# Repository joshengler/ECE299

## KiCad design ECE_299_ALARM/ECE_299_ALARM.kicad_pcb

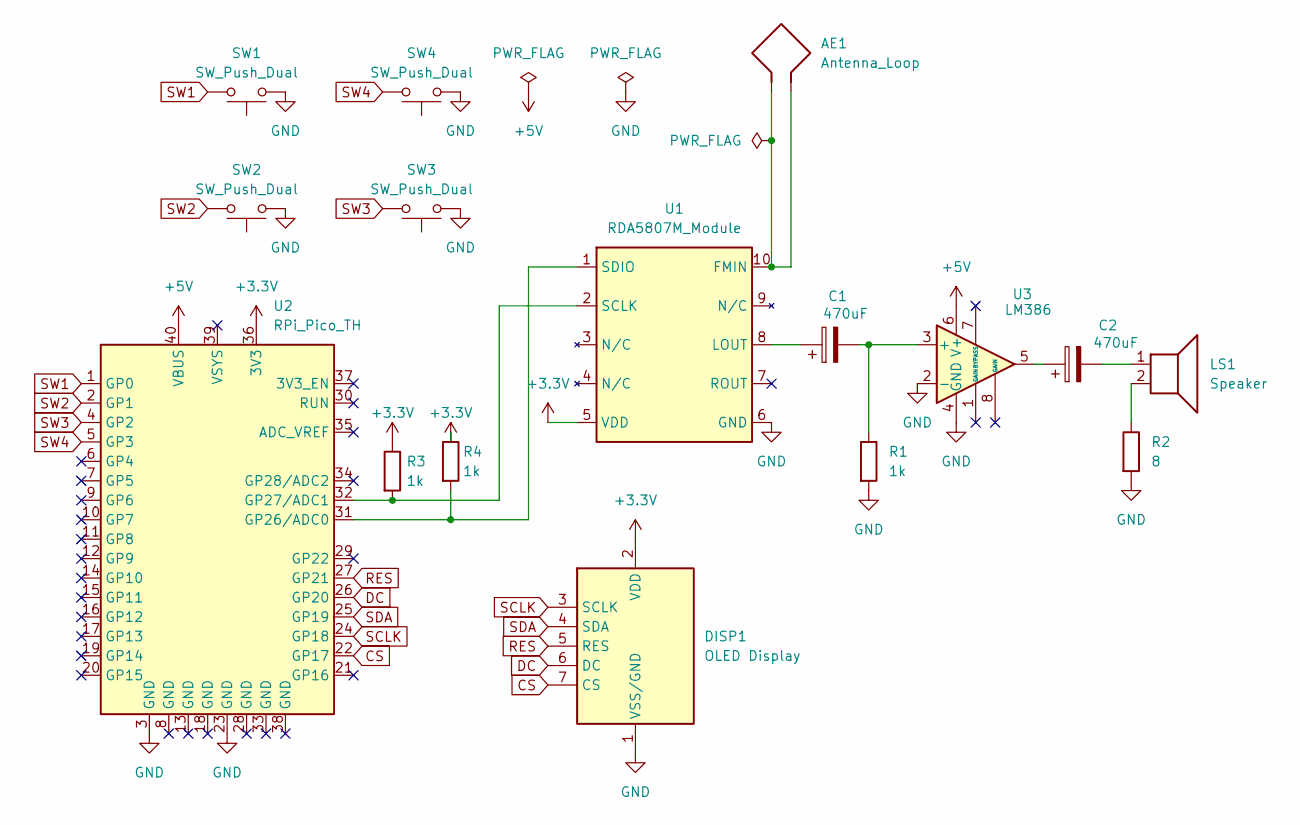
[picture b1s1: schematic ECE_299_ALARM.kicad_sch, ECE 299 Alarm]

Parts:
AE1: Antenna_Loop; PinHeader_1x02_P1.00mm_Vertical
C1, C2: 470uF; C_Radial_D6.3mm_H11.0mm_P2.50mm
DISP1: OLED Display; OLED_Display_1.3
LS1: Speaker; PinHeader_1x02_P2.54mm_Vertical
R1, R3, R4: 1k; R_Axial_DIN0309_L9.0mm_D3.2mm_P12.70mm_Horizontal
R2: 8; R_Axial_DIN0309_L9.0mm_D3.2mm_P12.70mm_Horizontal
SW1, SW2, SW3, SW4: SW_Push_Dual; SW_PUSH_6mm_H4.3mm
U1: RDA5807M_Module; RDA5807M_Module_SM
U2: RPi_Pico_TH
U3: LM386; DIP-8_W7.62mm

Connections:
+3.3V: DISP1.2 (VDD), R3.1, R4.1, U1.5 (VDD), U2.36 (3V3)
+5V: U2.40 (VBUS), U3.6 (V+)
CS: DISP1.7 (CS), U2.22 (GP17)
DC: DISP1.6 (DC), U2.26 (GP20)
GND: DISP1.1 (VSS/GND), R1.2, R2.2, SW1.1, SW2.1, SW3.1, SW4.1, U1.6 (GND), U2.3 (GND), U2.23 (GND), U3.2 (-), U3.4 (GND)
unnamed: C2.1, U3.5
unnamed: C2.2, LS1.1
unnamed: LS1.2, R2.1
unnamed: AE1.1, AE1.2, U1.10 (FMIN)
unnamed: C1.1, U1.8 (LOUT)
unnamed: R3.2, U1.2 (SCLK), U2.32 (GP27/ADC1)
unnamed: R4.2, U1.1 (SDIO), U2.31 (GP26/ADC0)
unnamed: C1.2, R1.1, U3.3 (+)
RES: DISP1.5 (RES), U2.27 (GP21)
SCLK: DISP1.3 (SCLK), U2.24 (GP18)
SDA: DISP1.4 (SDA), U2.25 (GP19)
SW1: SW1.2, U2.1 (GP0)
SW2: SW2.2, U2.2 (GP1)
SW3: SW3.2, U2.4 (GP2)
SW4: SW4.2, U2.5 (GP3)

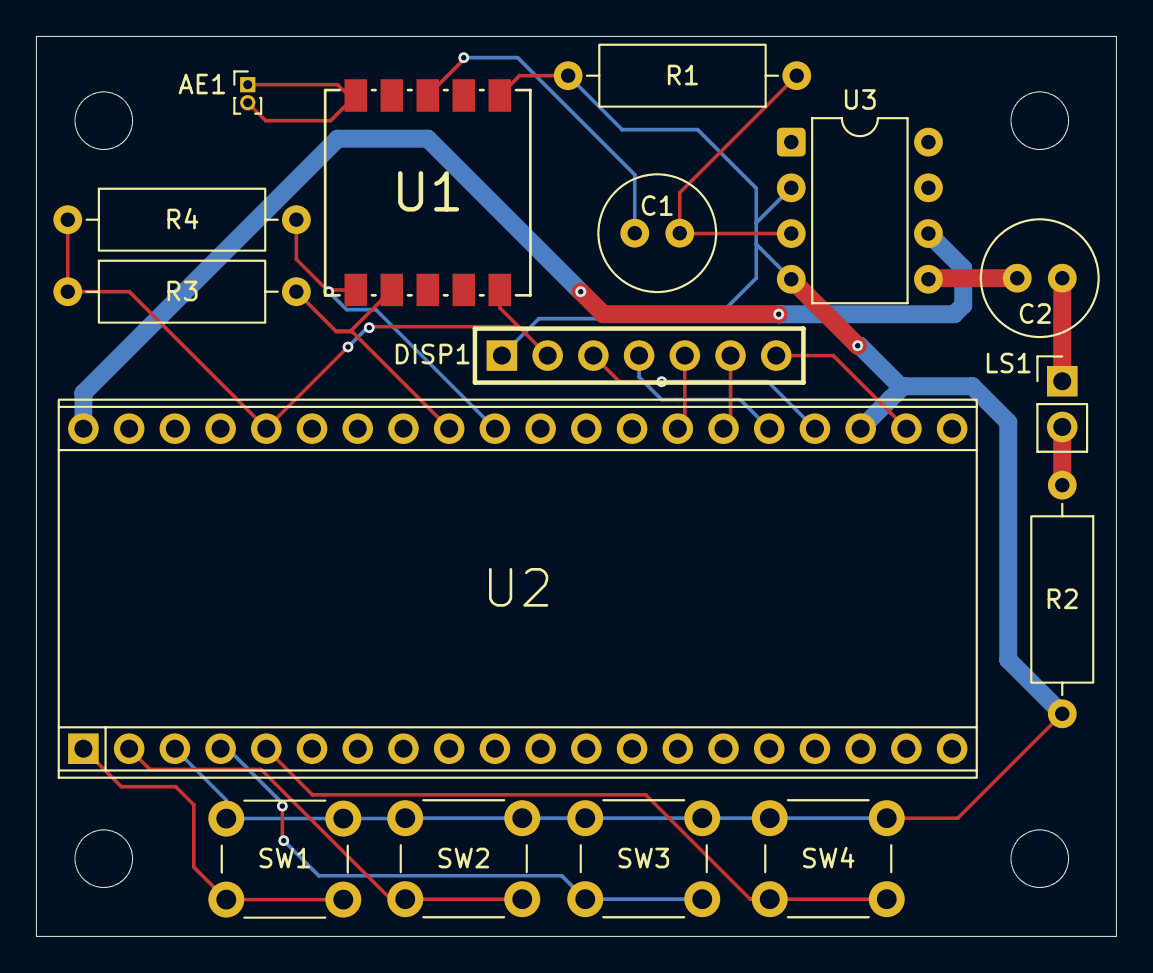
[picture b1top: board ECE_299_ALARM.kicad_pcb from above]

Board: 2 copper layers, 60.0 x 50.0 mm, 16 parts (0 on the bottom side), 20 nets.

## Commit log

2025-06-17 add vol, freq and mute controls to radio, still buggy but poc
2025-06-18 add vscode build, to avoid using thonny. requires mpremote
2025-06-18 fix vscode console output
2025-06-18 switch to alternative library, somehow the waveforms are cleaner on this lib, this library also gives better low level control + RDS
2025-06-18 various audio quality fixes, some cleanup
2025-06-18 add RSSI
2025-06-18 scuffed RDS implementation, very buggy atm
2025-06-18 remove rds, clean up dead/old code
2025-06-18 working rds support, needs strong signal tho
2025-06-18 disable rds for now
2025-06-20 add start of schematic
2025-06-22 added web app files
2025-06-22 commented out radio dependencies because my board doesnt have a radio module
2025-06-22 fixed URL from resubmitting queries when reloading the webpage
2025-06-22 moved html, css, js files a singular folder
2025-06-24 finish schematic
2025-06-24 remove lock
2025-06-24 add pullups on i2c
2025-06-24 fix antenna footprint
2025-06-24 fix antenna footprint (fr this time) also fix button footprint to be 2
2025-06-24 fix lm386-4 footprint
2025-06-24 garbage routing job completed
2025-06-25 add title and other info to sheet
2025-06-28 fixed typos
2025-06-28 browser should poll the board for any settings modified through hardware and update as needed
2025-07-07 added styles
2025-07-07 added support for changing alarm settings through a web interface
2025-07-09 added pcb files
2025-07-09 Revert "Web app"
2025-07-14 fix silkscreen overlap
2025-07-14 generate gerbers + drill
2025-07-25 error handling for radio and update pcb
2025-07-26 fix swapped SDA and SCL on radio module
2025-07-26 i just wasted an hour making better routing
2025-07-26 add high current path, 1mm is probably excessive
2025-07-26 small_adjustments
2025-07-26 realized i also need to make the power supply lines wider too...
2025-07-26 regenerate gerbers and drills
2025-07-26 remove locks
2025-07-26 add bar graph, STOP SCREAMING AT THE USER (caps) and various fixes (spi clock reduction to remove ticking) et al
2025-07-26 fix alarm toggling radio, added invert flashing on alarm trigger ->> should still test this but i believe it works
2025-07-26 minor formatting, yes the alarm triggers (both manually and by timer)
2025-07-26 readd web app
2025-07-26 add menu bar
2025-07-26 improve menu bar
2025-07-27 change i2c port + pins, slight refactor
2025-07-27 softblend enable/disable test
2025-07-27 add dRTC
2025-07-27 add rtc driver (oops) and remove snooze instructions as they are outdated
2025-07-27 fix syntax err
2025-07-27 add working webapp
2025-07-27 fix radio being muted when switching via web app
2025-07-27 add radio tuning+vol functionality to webapp
2025-07-27 fix err addrinuse by reusing the socket
2025-07-27 some css cleanup, but not much cuz im lazy, just enough to center the radio controls
2025-07-27 fix some desync between the two interface issues, many remain
2025-07-27 implement jump to host system time, webapp
2025-07-27 implement timer as special case of alarm
2025-07-27 auto enable alarm on set
2025-07-27 some more button fixes
2025-07-27 fix bug with alarm not updating on web app when changed on hardware IFACE. fix snooze notification being on line that is overwritten by setting selector text
2025-07-27 better faster timer logic
2025-07-27 remove 12 hour support
2025-07-27 fix bug with autoset time introduced by nuking 12 hr support
2025-07-28 working 12 hour support with client syncing
2025-07-28 adjust alarm toggle style
2025-07-28 attempt to fix bug with both 12/24 hr selection boxes accessible at once
2025-07-28 default vol 0
2025-07-28 small driver changes and ui changes, remove dead code
2025-07-28 various optimizations
2025-07-28 make debug output optional, more dead code removal
2025-07-28 test getting temperature from rtc because it has temp control oscillator
2025-07-29 other simplifications and cleanup
2025-07-30 add utc for exceeding expectations
2025-07-31 increase max volume, adjust label
